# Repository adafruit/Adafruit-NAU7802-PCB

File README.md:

## Adafruit NAU7802 24-Bit ADC - STEMMA QT / Qwiic PCB

<a href="http://www.adafruit.com/products/4538"><br/>
Click here to purchase one from the Adafruit shop</a>

PCB files for the Adafruit NAU7802 24-Bit ADC - STEMMA QT / Qwiic. 

Format is EagleCAD schematic and board layout
* https://www.adafruit.com/product/4538

### Description

If you are feeling the stress and strain of modern life a Wheatstone bridge and you want to quantify it, this handy breakout will do the job, no sweat! The Adafruit NAU7802 contains a super-high-resolution 24-Bit differential ADC with extra gain and calibration circuitry that makes it perfect for measuring strain gauges / load cells or other sensors that have four wires that are connected in a Wheatstone bridge arrangement.

Each breakout comes with a NAU7802 ADC chip, plus some support circuitry, and 4 terminal blocks that can be used to connect a 4-wire sensor.

The E- pad connects to ground (often a black wire), the E+ pad connects to a generated voltage from the NAU7802 that can be configured from 2.4V to 4.0V for a solid positive reference (often a red wire).

Then A- and A+ pads connect to the differential outputs from the bridge. For example, connecting to a strain gauge these tend to be the white and green wires.

As the sensor is twisted and bent, the slight changes in resistance are converted to minuscule voltage changes that can be read by the NAU ADC for converting into force or mass measurements. You can use our Arduino library or CedarGrove's CircuitPython/Python library to configure and read the ADC for fast interfacing. Note that this sensor has a fixed I2C address, if multiple sensors are desired on one I2C bus, a multiplexer can be used.

### License

Adafruit invests time and resources providing this open source design, please support Adafruit and open-source hardware by purchasing products from [Adafruit](https://www.adafruit.com)!

Designed by Limor Fried/Ladyada for Adafruit Industries.

Creative Commons Attribution/Share-Alike, all text above must be included in any redistribution. 
See license.txt for additional details.

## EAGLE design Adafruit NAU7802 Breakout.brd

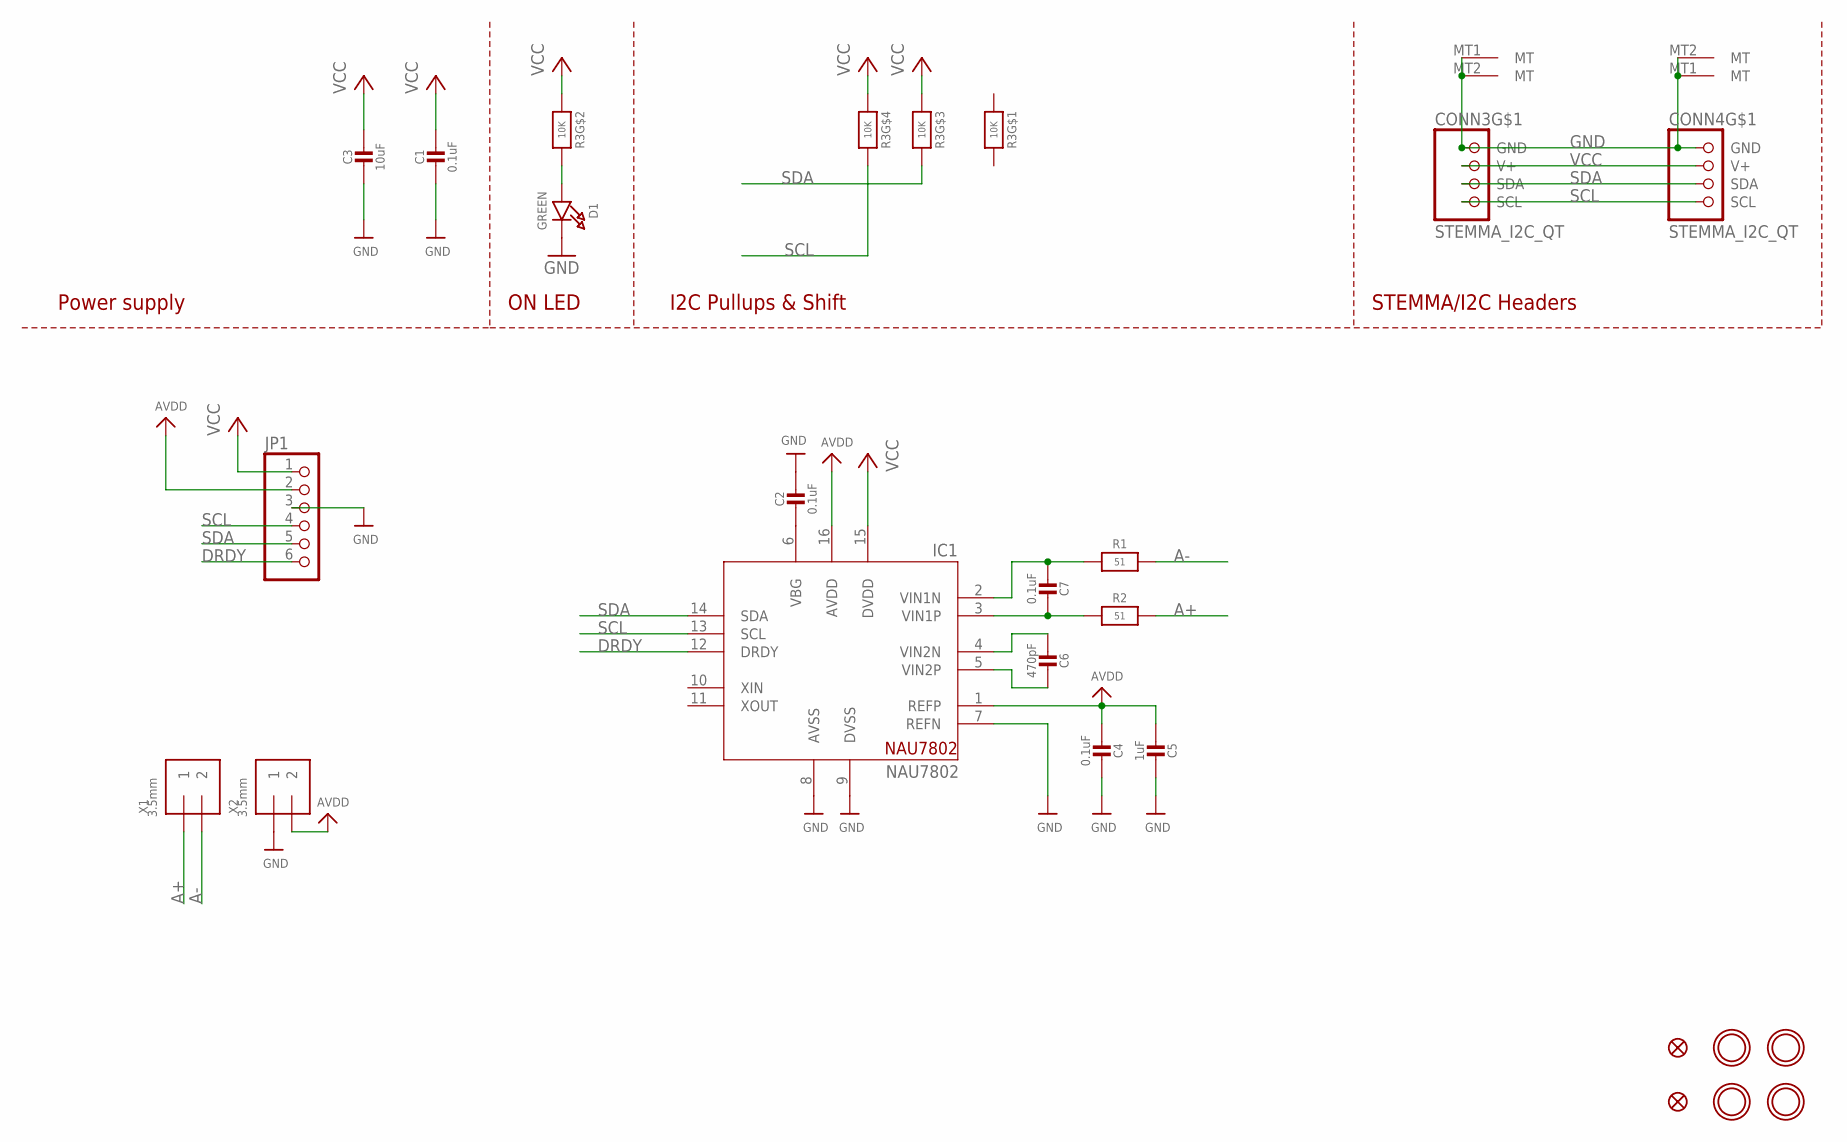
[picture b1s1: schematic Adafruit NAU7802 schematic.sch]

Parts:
C1, C2, C4, C7: 0.1uF; 0603-NO
C3: 10uF; 0805-NO
C5: 1uF; 0603-NO
C6: 470pF; 0603-NO
CONN3, CONN4: STEMMA_I2C_QT; JST_SH4
D1: GREEN; CHIPLED_0603_NOOUTLINE
FID3, FID4: FIDUCIAL_1MM
IC1: NAU7802; SOIC16_NARROW
JP1: HEADER-1X670MIL; 1X06_ROUND_70
R1, R2: 51; 0603-NO
R3: 10K; RESPACK_4X0603
U$1, U$17, U$19, U$21: MOUNTINGHOLE2.5; MOUNTINGHOLE_2.5_PLATED
X1, X2: 3.5mm; TERMBLOCK_1X2-3.5MM

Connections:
A+: R2.2, X1.1
A-: R1.2, X1.2
AVDD: C4.2, C5.2, IC1.1 (REFP), IC1.16 (AVDD), JP1.2, X2.2
DRDY: IC1.12 (DRDY), JP1.6
GND: C1.2, C2.1, C3.2, C4.1, C5.1, CONN3.1 (GND), CONN3.MT1 (MT), CONN3.MT2 (MT), CONN4.1 (GND), CONN4.MT1 (MT), CONN4.MT2 (MT), D1.C, IC1.7 (REFN), IC1.8 (AVSS), IC1.9 (DVSS), JP1.3, X2.1
unnamed: D1.A, R3.7 (2)
unnamed: C2.2, IC1.6 (VBG)
unnamed: C6.2, IC1.4 (VIN2N)
unnamed: C6.1, IC1.5 (VIN2P)
unnamed: C7.1, IC1.3 (VIN1P), R2.1
unnamed: C7.2, IC1.2 (VIN1N), R1.1
SCL: CONN3.4 (SCL), CONN4.4 (SCL), IC1.13 (SCL), JP1.4, R3.5 (2)
SDA: CONN3.3 (SDA), CONN4.3 (SDA), IC1.14 (SDA), JP1.5, R3.6 (2)
VCC: C1.1, C3.1, CONN3.2 (V+), CONN4.2 (V+), IC1.15 (DVDD), JP1.1, R3.2 (1), R3.3 (1), R3.4 (1)

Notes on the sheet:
I2C Pullups & Shift
STEMMA/I2C Headers
ON LED
Power supply

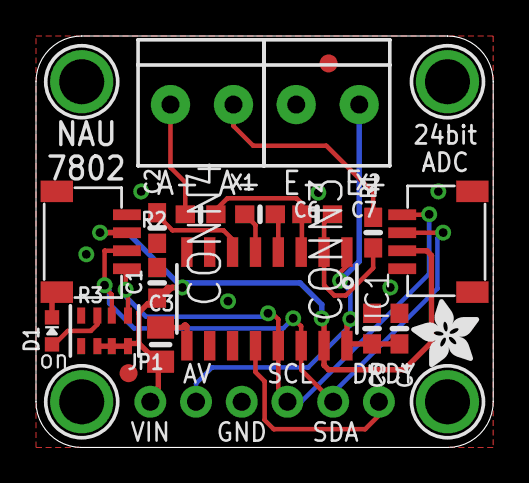
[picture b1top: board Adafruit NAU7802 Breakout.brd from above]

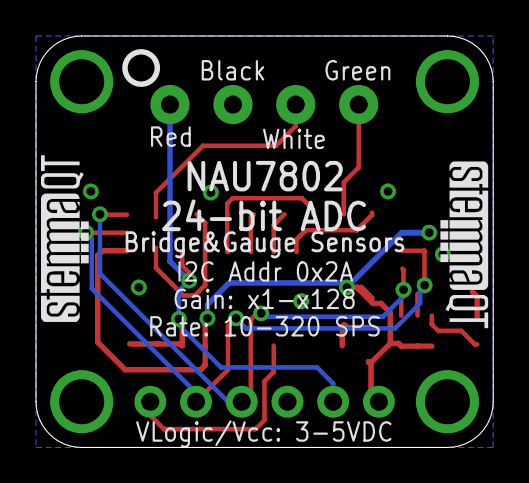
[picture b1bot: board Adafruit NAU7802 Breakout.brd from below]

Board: 2 copper layers, 25.4 x 22.9 mm, 27 parts (3 on the bottom side), 14 nets.

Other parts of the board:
U$22: ADAFRUIT_3.5MM
U$25: PCBFEAT-REV-040
U$30, U$31: STEMMAQT

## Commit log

2022-05-24 Adding cookiecutter output
    Adding schematic, board file and cookiecutter output
2023-02-01 updating name

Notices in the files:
parts and their libraries:
microbuilder: This work is placed in the public domain, and may be freely used for commercial and non-commercial work with the following conditions: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
